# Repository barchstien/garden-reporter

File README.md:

[TOC]

# Overview

Collect data about the garden (soil humidity, luminosity and temperature), that is gathered via xbee link to the collector, for storage and visualisation.

Control and measure water flow. It flows when it is programmed to, or when manually triggered for a set duration.

Xbee modules are configured to :
 - cycle sleep to probe every 15min and stay ON for around 100 msec
 - send data to the collector

## UI and Configuration
 * Collector is configured via YAML, see [collector](/collector/) folder
 * Probes are configured when deployed, by uploading the profile (see profile*.xpro files)
 * Visulisation via Grafana
 * Water-control polls the set program every time it reports water flow
 * Water flow program is configured via web UI

# Probe
More doc about probe in [probe/](/probe)

# Collector
More doc about collector in [collector/](/collector)

# Water-control
More doc about water-control in [water-control/](/water-control)

# grafana-dashboards
Collection of grafan dashboards, exported as JSON, [here](/grafana-dashboards)

# resources
Images and diagrams

# IRL
The system has been running as a prototype since autumn 2022. Thought, after 2 months, the deployed probes started to randomly block, ie not wake up anymore, until it was rebooted. It got fixed only after changing the sleep switch (mosfet) from low side to high side. Cutting the low side was leading some voltage values to go beyond Xbee specs.

The v2 probe have been running since early february 2023. Two other probes have been deployed in mid-february and mid-april 2023. As of end of july 2023, they all perform within nominal parameters.

So far, I have used a COTS water programmer (jardibric PNR16). Which has been working fine. Thought it cannot be programmed to water at a chosen time, nor can it be easily triggered randomly without messing with the set program.

Water flow is also measured using a mechanical water counter found in the local hardware store.

## Visualisation

## Probe

## Collector

## Water-control
Coming soon

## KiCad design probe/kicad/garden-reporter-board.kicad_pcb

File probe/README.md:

# Overview

## Features
 - Probe for :
   - soil humidity
   - air temperature
   - luminosity
   - battery level
 - 6 month+ battery (1 year). See **probe-board-power-use.ods**
 - Report to collector
   - via xbee 2.4GHz 802.15.4
   - every 15min using cycle sleep

Kicad files are in **probe/kicad** folder  
Components datasheet are in **probe/datasheet** folder  

## Board 3d view

# Mechanic and water consideration
 - case should be wateproof
   - plastic bottles are inexpensive and water proof
     - bottom is filled with gravel for stability and in case of leak
   - sensors are attached to case
   - wires from sensors to probe board are water resistent
     - use plumbing goo/joint/paste
   - sensors are environment protected :
     - luminosity is already in epoxy case, wire nail polished
     - temp and wires are nail polished
     - soil moisture bottom is (home made) epoxy coated (water + abrasive)
     - soild moisture top is nail polished

# Components
**Note :** [XXX-XX] : mouser order number

## Xbee
 * XB24CAPIT-001, TH, s2c 802.15.4 [888-XB24CAPIT-001]
    - give 1uF and 8pf cap on supply
    - good keepout (bigger better, no gnd plane up), for pcb antenna
 * usb adapter
    - usb explorer board from sparkfun WRL-11812 [474-WRL-11812] 26.33E
    - dfrobot DFR0050 [426-DFR0050] 18.95E

## Switch
 * TN0702N3-G, can switch 20V, on at 1V, 0.1uA stdby  
   1.53E [689-TN0702N3-G]  
 * Use flywheel diode to protect mosfet from switched inductive load  
   SB130 [637-SB130]
 
## Battery 
 * 4x AA Nimh 2000mAh low self-discharged
   - Accus hybrides Aeonium - 2100mAh 8E for 4, 85% after 1 year
   - Energizer accu recharge extreme 2000mAh 8.6E for 4
 * 4x battery holder 58x31x28 12BH343D-GR [12BH343D-GR]
   OR 534-2476 with snap-on ?  
 Nimh nominal/min/max voltage 1.2/0.9/1.5  
 with 4 cells 4.8/3.6/6V 

## 3.3V voltage regulator
 * MCP1700-3302E/TO 0.5E [579-MCP1700-3302E/TO]  
   Vin 2.3 to 6V, Vdrop typical 178mV, max 350mV  
   250 mA max output  
   Use 1uF co at output (and 1 at input ?)  
 
## Soil moisture sensor
Capacitor sensor  
  * SEN0193 DFRobot 7.9E [426-SEN0193]  
   |--> Protect with nail polish
   |--> been using that one at first. Wire wares off with UV  
        nail polish coating seams to hold fine after 1.5 year  
  * SEN0308 DFRobot 15E [https://wiki.dfrobot.com/Waterproof_Capacitive_Soil_Moisture_Sensor_SKU_SEN0308]  
   |--> Now uses that one, goes deeper, better wire, only nail polish coat the PCB edge
   |--> Use extra 55KOhm in serie of signal, solder in wire  
        This gives ADC values around [75; 800]  
  * 3.3V 5mA  
  * **Warning** some cheapper alternative exists but aren't documented, nor reliable  

## Temp sensor
 * TMP36GT9Z [584-TMP36GT9Z] 1.81E  
   Must add O.1uF cap, very close to device, ie on wire

## Photo transistor
 * TEPT5700 [782-TEPT5700]  
   Use with 5K resistor for outside use with diffuser, measure U, then I = U/R  
   From I, get Lux, using calibration with a ref lux meter  
 The value of R will set the sensibility and saturation level  
 Use with a diffuser, to mitigate the effect of the angle towards the light source  
 
 For inside use, use a higher R value. 
 Aiming 5000 Lux max inside, which is 1/10 of outside max use
 Outside uses 5K --> use 50K --> only have 2x 20K

## Battery level sensor
 * Add battery level check with voltage divider  
   with 2x 10K resitor 1%  
   with zener diode 1N4620 3.3V, [610-1N4620BK]

## Connector
 * sensor to board, 3ways
  - 70543-0002 [538-70543-0002] pcb straigth header  
    70543-0107 for even more gold plating !
  - 79758-0011 [538-79758-0011] crimped wire, 30cm, 22awg
  - 50-57-9403 [538-50-57-9403  ] cable mount
 * battery to board, same with 2 pins
   [538-70543-0106]
 * Use kicad Molex_SL_171971
 
## Case
 * bicycle bottle, ~750mL, 20cm high, 7cm diameter

## Various
 * R 10K 1% metal film : [603-MFR-25FRF5210K]
 * c 10uF ceramic : [710-860010472002] 25VDC 85degC max
 * C 1uF ceramic : [810-FG18X7R1E105KRT0] 25VDC
 * c 8.2 pF ceramic : [80-C315C829D2G] 200VDC

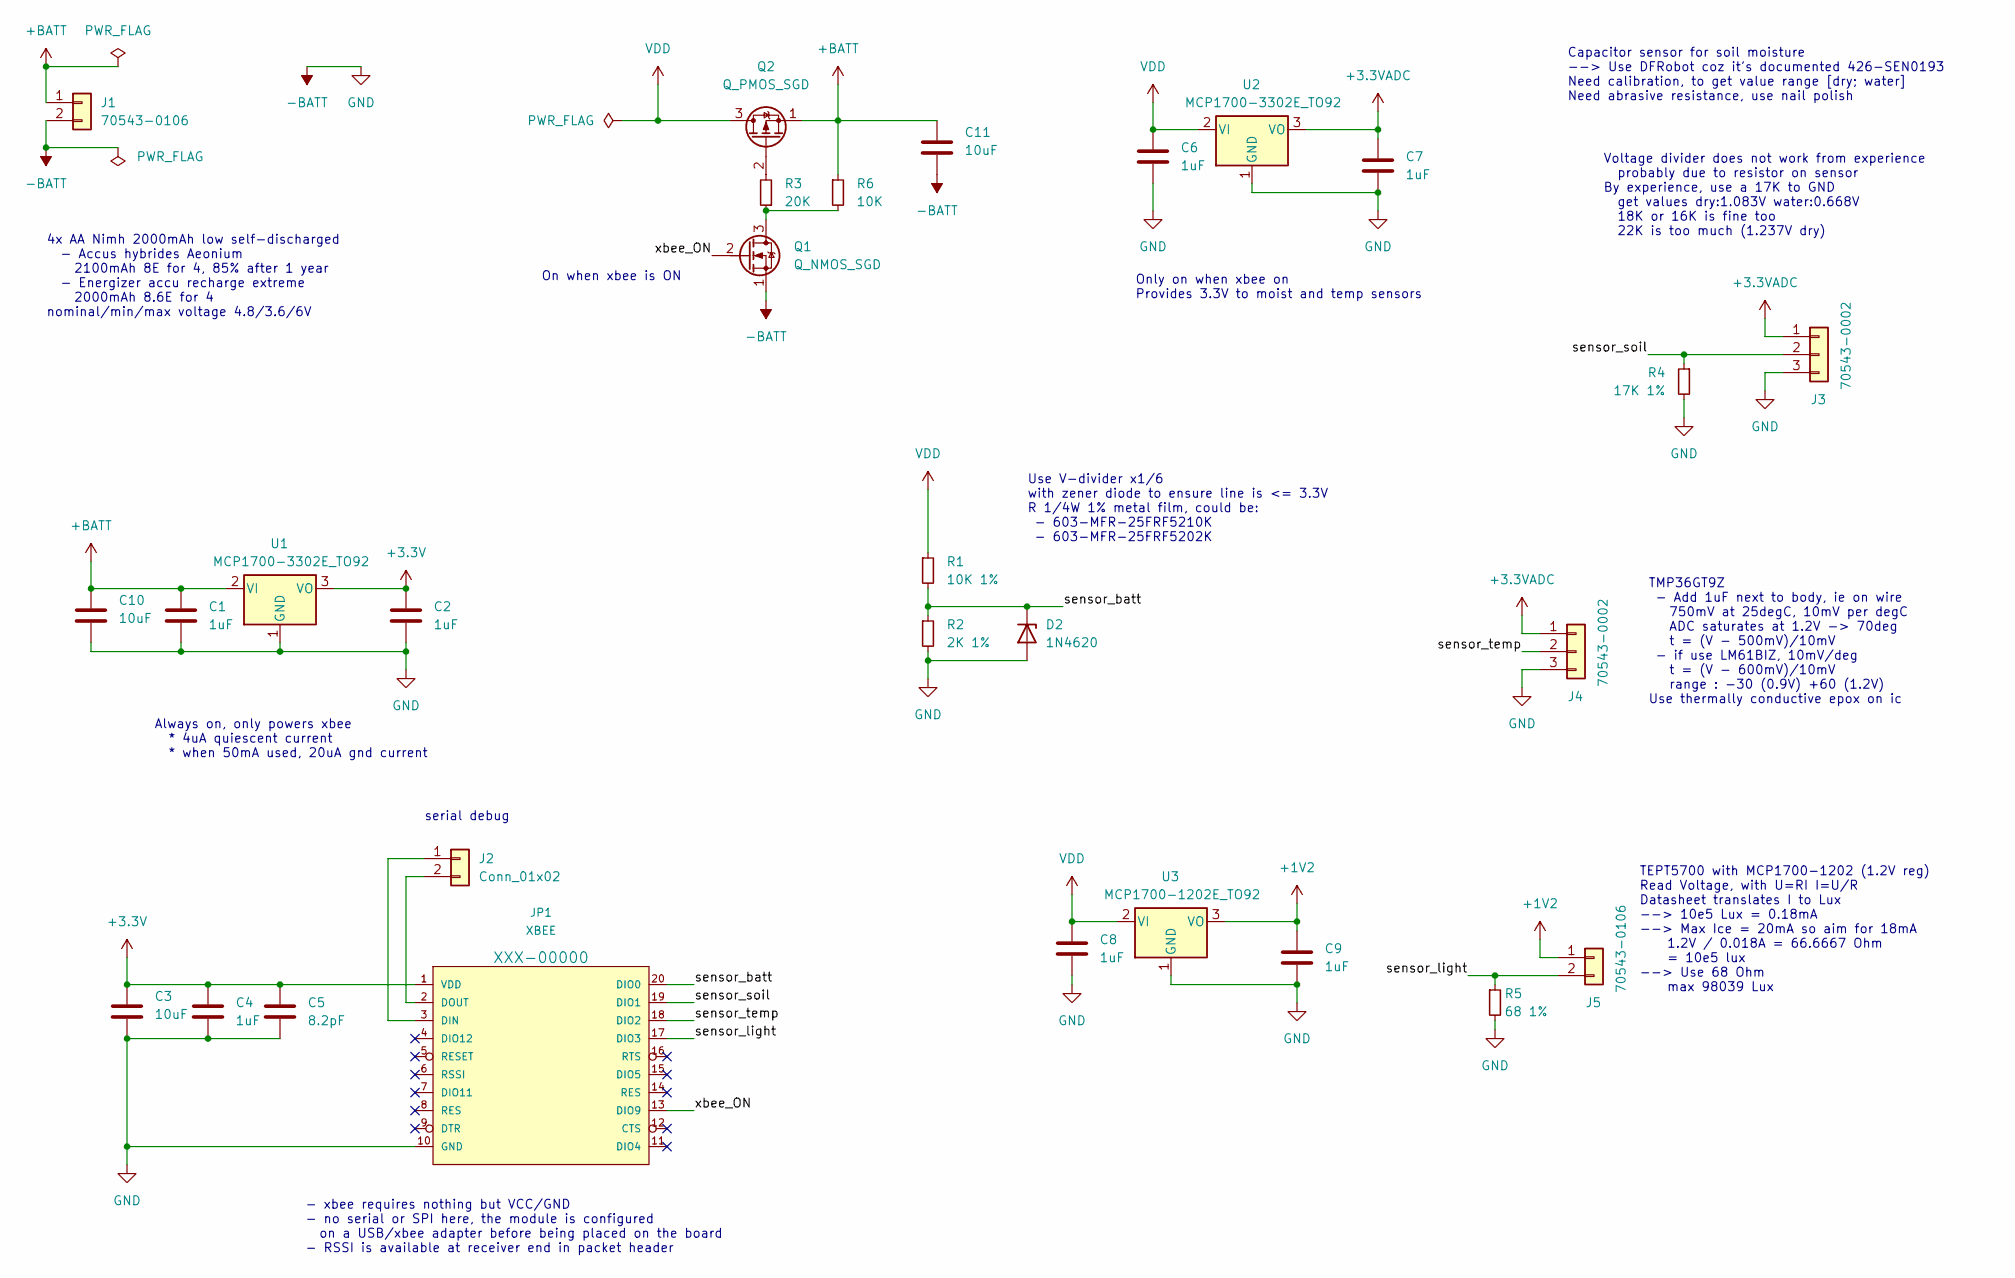
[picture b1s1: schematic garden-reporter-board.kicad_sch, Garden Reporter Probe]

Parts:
C1, C2, C4, C6, C7, C8, C9: 1uF; C_Disc_D3.0mm_W2.0mm_P2.50mm; mouser FG18X5R1H105KRT06
C3, C10, C11: 10uF; C_Disc_D5.0mm_W2.5mm_P2.50mm; mouser 810-FG18X5R1E106MR06
C5: 8.2pF; C_Disc_D3.8mm_W2.6mm_P2.50mm; mouser 80-C315C829D2G
D2: 1N4620; D_DO-35_SOD27_P7.62mm_Horizontal; mouser 610-1N4620BK
J1, J5: 70543-0106; Molex_SL_171971-0002_1x02_P2.54mm_Vertical; mouser 538-70543-0106
J2: Conn_01x02; PinHeader_1x02_P2.54mm_Vertical
J3, J4: 70543-0002; Molex_SL_171971-0003_1x03_P2.54mm_Vertical; mouser 538-70543-0002
JP1: XBEE; mouser 710-62001011821
Q1: Q_NMOS_SGD; TO-92_Inline; mouser 689-TN0702N3-G
Q2: Q_PMOS_SGD; TO-92_Inline; mouser 689-VP3203N3-G
R1: 10K 1%; R_Axial_DIN0207_L6.3mm_D2.5mm_P7.62mm_Horizontal; mouser 603-MFR-25FRF5210K
R2: 2K 1%; R_Axial_DIN0207_L6.3mm_D2.5mm_P7.62mm_Horizontal; mouser 603-MFR-25FRF522K
R3: 20K; R_Axial_DIN0207_L6.3mm_D2.5mm_P7.62mm_Horizontal; mouser 603-MFR-25FRF5220K
R4: 17K 1%; R_Axial_DIN0207_L6.3mm_D2.5mm_P7.62mm_Horizontal; mouser 603-MFR-25FTF52-17K
R5: 68 1%; R_Axial_DIN0207_L6.3mm_D2.5mm_P7.62mm_Horizontal; mouser 279-LR0204F68R
R6: 10K; R_Axial_DIN0207_L6.3mm_D2.5mm_P7.62mm_Horizontal; mouser 603-MFR-25FRF5210K
U1, U2: MCP1700-3302E_TO92; TO-92_Inline; mouser 579-MCP1700-3302E/TO
U3: MCP1700-1202E_TO92; TO-92_Inline; mouser 579-MCP1700-1202E/TO

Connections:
+1V2: C9.1, J5.1, U3.3 (VO)
+3.3V: C2.1, C3.1, C4.1, C5.1, JP1.1 (VDD), U1.3 (VO)
+3.3VADC: C7.1, J3.1, J4.1, U2.3 (VO)
+BATT: C1.1, C10.1, C11.1, J1.1, Q2.1 (S), R6.1, U1.2 (VI)
-BATT: C1.2, C2.2, C3.2, C4.2, C5.2, C6.2, C7.2, C8.2, C9.2, C10.2, C11.2, D2.2 (A), J1.2, J3.3, J4.3, JP1.10 (GND), Q1.1 (S), R2.2, R4.2, R5.2, U1.1 (GND), U2.1 (GND), U3.1 (GND)
/sensor_batt: D2.1 (K), JP1.20 (DIO0), R1.2, R2.1
/sensor_light: J5.2, JP1.17 (DIO3), R5.1
/sensor_soil: J3.2, JP1.19 (DIO1), R4.1
/sensor_temp: J4.2, JP1.18 (DIO2)
/xbee_ON: JP1.13 (DIO9), Q1.2 (G)
unnamed: J2.1, JP1.3 (DIN)
unnamed: J2.2, JP1.2 (DOUT)
unnamed: Q1.3 (D), R3.1, R6.2
unnamed: Q2.2 (G), R3.2
VDD: C6.1, C8.1, Q2.3 (D), R1.1, U2.2 (VI), U3.2 (VI)

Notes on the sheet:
- xbee requires nothing but VCC/GND - no serial or SPI here, the module is configured on a USB/xbee adapter before being placed on the board - RSSI is available at receiver end in packet header
Voltage divider does not work from experience probably due to resistor on sensor By experience, use a 17K to GND get values dry:1.083V water:0.668V 18K or 16K is fine too 22K is too much (1.237V dry)
Use V-divider x1/6 with zener diode to ensure line is <= 3.3V R 1/4W 1% metal film, could be: - 603-MFR-25FRF5210K - 603-MFR-25FRF5202K
Always on, only powers xbee * 4uA quiescent current * when 50mA used, 20uA gnd current
4x AA Nimh 2000mAh low self-discharged - Accus hybrides Aeonium 2100mAh 8E for 4, 85% after 1 year - Energizer accu recharge extreme 2000mAh 8.6E for 4 nominal/min/max voltage 4.8/3.6/6V
Only on when xbee on Provides 3.3V to moist and temp sensors
TMP36GT9Z - Add 1uF next to body, ie on wire 750mV at 25degC, 10mV per degC ADC saturates at 1.2V -> 70deg t = (V - 500mV)/10mV - if use LM61BIZ, 10mV/deg t = (V - 600mV)/10mV range : -30 (0.9V) +60 (1.2V) Use thermally conductive epox on ic
On when xbee is ON
Capacitor sensor for soil moisture --> Use DFRobot coz it's documented 426-SEN0193 Need calibration, to get value range [dry; water] Need abrasive resistance, use nail polish
serial debug
TEPT5700 with MCP1700-1202 (1.2V reg) Read Voltage, with U=RI I=U/R Datasheet translates I to Lux --> 10e5 Lux = 0.18mA --> Max Ice = 20mA so aim for 18mA 1.2V / 0.018A = 66.6667 Ohm = 10e5 lux --> Use 68 Ohm max 98039 Lux

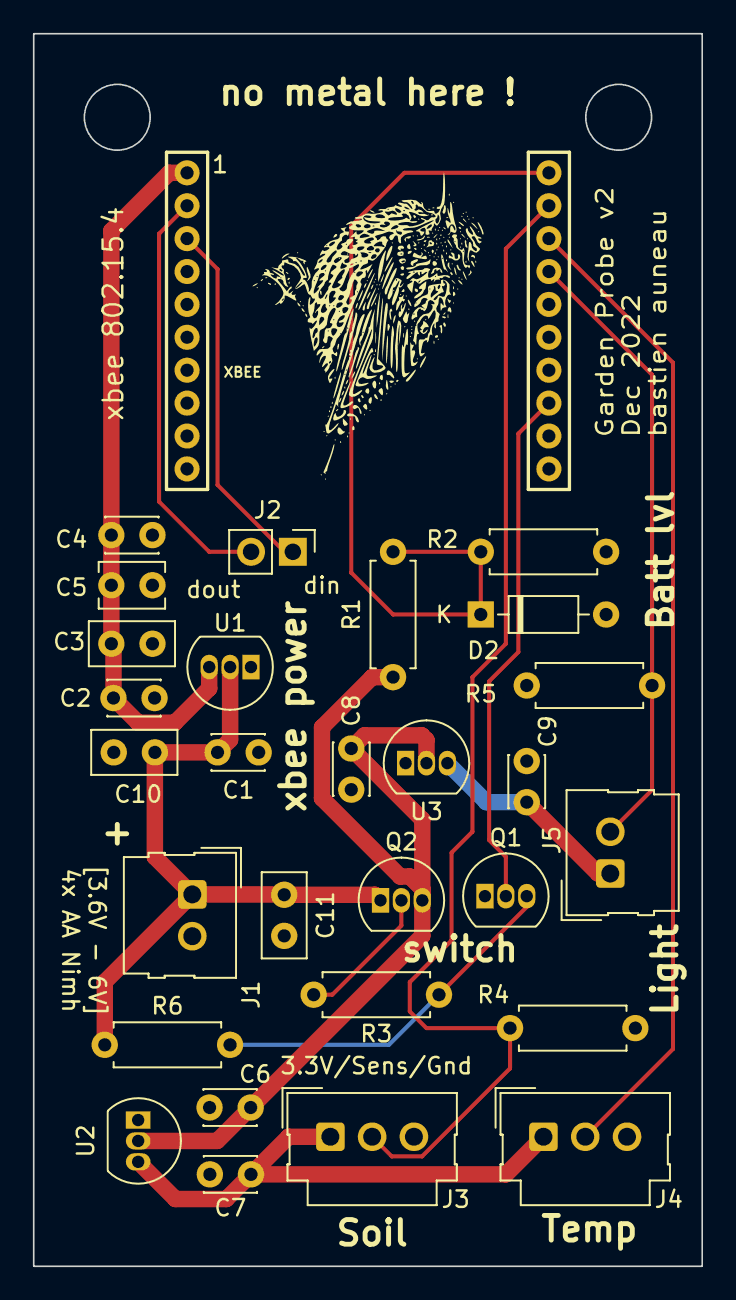
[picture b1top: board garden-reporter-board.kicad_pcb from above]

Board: 2 copper layers, 40.6 x 74.9 mm, 29 parts (0 on the bottom side), 15 nets.

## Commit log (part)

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2022-08-12 Initial commit, removed previous history which was bloated with kicad backup and cache files
2022-08-21 Feature/probe pcb edge and routing
2022-08-21 Smaller mouting holes
2022-08-22 Fix bad flyback diode connection, move xbee edge drawing to fron silkscreen
2022-08-22 Add artichoke picture, add and ùake pretty silkscreen comments
2022-08-22 Pretty
2022-08-29 Feature/better doc
2022-09-04 Doc on not using telegraf
2022-09-06 Start collector, re-organize folders
2022-09-24 Feature/v divider for sensors
2022-09-24 Fix Xbee frame decoder bug, started SerialHub, add doc on xbee range
2022-09-24 Install pyyaml, load probes calib from yaml, and serial config and influxdb config from yaml too
2022-09-25 Better doc
2022-10-01 Add serial_hub
2022-10-02 serial_hub provides r a,d w queues. tcp_listener basic fwd
2022-10-03 Collector works, but XCTU can't connect
2022-10-03 tcp serial working
2022-10-03 Use custom channel id and PAN id, use 64bit addressing
2022-10-03 Use 64 bit ADC frame (x82)
2022-10-04 Notes on xbee API use
2022-10-12 Basic blocks decoding frames to dict, empty shell with interface for...
2022-10-12 sleep more, use less CPU (2.2 to 0.8%)
2022-10-12 Add XbeePopulationModel methods to hold or release endpoint in config. Start serial_tcp_client to handle creation and config on client side
2022-10-12 TcpListerner has ref to xbee popo model, fix socat call on tcp client script
2022-10-12 Better message
2022-10-12 SerialHub 1 thread to read and one to write, using blocking call for minimal CPU use
2022-10-12 socket accept blocking call and cancel with shutdown()
2022-10-12 serial hub read all available at once
2022-10-13 Use 1 thread to read 1 to write in TCP Listener, remove some traces
2022-10-13 Working TCP Listener that holds in config and exits properly
2022-10-13 serial-tcp-client has now help(), extracts all args from CLI, and runs socat
2022-10-13 TCP Listener waits for 8 bytes, and can cancel and fall back to normal mode
2022-10-13 seria tcp client sends MAC, listener receives it
2022-10-14 Tcp to serial have client and server negotiating for MAC to hold, and to wait for endpoint to be up and help (no cycle sleep)
2022-10-14 Send enable/disable Cycle Sleep when config mode is requested
2022-10-14 BEtter display reply status
2022-10-14 Encode value when needed, for SM AT cmd only
2022-10-14 Apply changes option when set/unset cycle sleep mode, do not wait for target when request mac 0
2022-10-15 Cleanup collector doc
2022-10-15 pipenv lock
2022-10-16 TODOs and docs on V-divider for light sensor
2022-10-19 Add basic Dockerfile add calib value for soil moisture on proto
2022-10-19 Pretty tcp serial client waiting msg
2022-10-29 Map soil moisture to percentage
2022-10-31 Docker working, update doc, fix showing all past errors on startup
2022-10-31 Notes on influxdb backup
2022-10-31 Add to light sensor V reg to 1.2V, adjust light R properly, fix layout accordingly
2022-10-31 Clean up old TODO, warning on soil moisture and V-divider
2022-10-31 Comment on soil moisture sensor and V-divider
2022-11-10 Fix trace bug
2022-11-10 Doc on batery life expectation
2022-11-11 Add profile cycle sleep 15min with 100msec sleep tiemout
2022-11-11 Run python with -u as unbuffered to get anything with docker logs
2022-11-11 Estimation max days by projection from measured use
2022-11-11 Working state ! Just pulling ADC once, been hacking model, and tuning sleep values
2022-11-11 Comments on hacks
2022-11-13 Xbee population model is executed by collector thread, hack message flow to only sample ADCs
2022-11-14 Poll errors when timeout occrs (24h), write error to db when there is, cleanup
2022-11-14 Update last error timestamp when recv error msg
2022-11-15 Collector uses blocking get() from Q, awakening is now down to 30-35msec per request
2022-11-15 Fix voltage output range of soil moist sensor, 1.2V to light sensor
2022-11-15 Fix crash and clean README
2022-11-17 Fix xbee not being released from config (ie not back to cycle sleep), due to population model being called only when frame is received. Now executing population model on frame RX timeout
2022-11-18 Try ax+b calibration
2022-11-18 Use ax+b to calibrate temp
2022-11-19 Adjust dry value
2022-11-22 Add exported dashboard json
2022-11-27 Light is percet
2022-11-28 More profile and dashbord backup
2022-11-28 Add lm61 and xbee grove usb datasheet
2022-12-09 Better doc on influxdb backup/restore
2022-12-09 Fix bug on TCP server when bad connection happen
2022-12-10 Add profile with cycle sleep disabled
2022-12-10 Add second xbee unit to config
2022-12-12 Better msg, dummy mac for 1s device
2022-12-14 Smaller profile. Re-number sensor mosfet pins properly
2022-12-18 Re-enable 1st unit MAC
2022-12-18 Cleanup notes in README
2022-12-18 Print frame received out of awakening, remove extra frame sent after awakening
2022-12-18 Add ceriamic cap for xbee and heavy load sensors, better routing of voltage regulator capacitors, more compact outline
2022-12-18 Add ceramic cap datasheet
2022-12-18 Also pull xbee for supply level, every time CC error is pulled, ie every 24h
2022-12-18 Routing decouple cap
2022-12-18 Fix bug and Better message on influx-db error
2022-12-23 Use high side switch, chose new components and footprints, layed out but no route, use GND plane, add doc and datasheet
2022-12-23 Route all
2022-12-24 Finish and verifiy routing, finish and verify BOM
2022-12-24 Add garden probe v2 gerber files
2023-02-07 High side switch working fine, fix few comments
2023-02-07 Latest profile, probably some tweaking
2023-02-07 Rename timeout for polling erro cnt
2023-02-07 Notes taken while investigating before going for high side switch
2023-02-07 Translate light ADC read into Lux
2023-02-08 Use v2 config for battery v divider, soil read range, default temperature formula
2023-02-08 Remove light coefficient from yaml and data_calibrator
2023-02-14 Add grafana dashboards
2023-02-14 Add R config to light sensor
2023-02-15 Add location as tag, force data type in influxdb write
2023-02-15 Update Grafana dashboards with location tag support
2023-02-16 Use windowPeriod and better names for grafana dashboards json export files
2023-02-26 Clean up xbee profiles
2023-02-26 Remove influxdb dashboards, replaced by grafana
2023-02-26 Remove old grafana dashboards
2023-02-26 Better grafana dashboards that inludes location, links, etc
2023-02-26 Cleanup
2023-02-26 More cleanup
2023-02-26 pip install as user, fix user home dir bug, cleanup
2023-02-26 Calibrate noisetier
2023-03-31 Calibraet light with ref
2023-04-03 Lower immerged value probe 1
2023-05-18 Unit #3 and more calibration
2023-05-21 Remove non used python yaml lib from pipenv
2023-05-21 New moist calibration for noisetier and potager nord
2023-07-29 Better organise doc in sub-folders
2023-07-29 Better alignment of probe doc
2023-07-29 TODO
2023-07-30 Basic html page, from a discussion with chatgpt
2023-07-30 Just before asking chatgpt to : make it look cool
2023-07-30 A bit larger box
2023-07-30 ASCII art git diff
2023-07-30 Move html to python folder
2023-07-30 Basic python server serves modified html file
2023-07-30 Add more paths to poll and update
2023-08-02 Basic web server, handles requests, feed prams
2023-08-02 Pretty ascii
2023-08-07 /report gets values and ecoes back as json
2023-08-07 Add arduino workspace
2023-08-08 Basic structure and main function for wifi and pin settings
2023-08-09 basic http GET and basic valve control
2023-08-15 Doc on power use. Basic buttons working. Add TimeLib simplified biiig time, better interface
2023-08-15 time_lib better naming and simplified
2023-08-16 Proto to get time from http server
2023-09-03 Test mode and doc on pin numbering vs arduibox
2023-10-10 Button test success
2023-10-14 Add robot favicon
2023-10-22 Basic debug loop
2023-11-25 Add unit #4, consider unit without soil recording
2023-11-25 Fix end point profile, doc
2023-11-29 Better light calibration for indoor unit
2024-02-24 Maison unit better calib
2024-06-04 Http server for human and machine first proto
2024-06-07 Basic request and replay working between water-controller and server
2024-06-07 wifi client reports to server and propagate command
2024-06-08 Battery, buttons, time sync, report all work
2024-06-11 Schedule can be config from WEB UI, and propagates to arduino. Arduino reports voltage and water volume
2024-06-13 Better local clock vs epoch time from server
2024-06-14 Better epoch sync, clean up, start bringing real status of arduino to web UI
2024-06-14 time sync working like a charm, use msec counter to avoid stacking up rounding errors
2024-06-15 Display valve status
2024-06-15 Report valve status, count wraps to provide uptime
2024-06-15 Usable proto, stop using cgi even for POST
2024-06-16 Longer valve pulse (1sec), longer max duration (1.5h), check allow water button when schedule watering, led off fix
2024-06-18 Calibrate water counter, remove debug traces, use Threading HTTP server, count sum of drifts
2024-06-21 Many bug fixes (re-schedule, led, time sync, http response wait
2024-06-23 Retry HTTP request few times before giving up
2024-06-23 Less log
2024-06-23 Way clearer local vs epoch clock, use RTC backeend for epoch, update value from server when over threshold, local_clock_t reconstructs higher bits to hide wrap
2024-06-23 Remove python basee HTTP server log
2024-06-24 15min between HTTP reports, better scale web human UI to mobile phone
2024-06-24 Better calib, set max size for container log in restart script
2024-06-24 First proto, should disable other modeules for tests
2024-06-24 Write water web control volume and battery in db
2024-06-26 Report when water triggered manually, use RTC clock coz millis() drift wayyyy to much
2024-06-26 Use named volume for water-web-control config, fix docker files rights, write water usage in db
2024-06-26 Remove some print in water web server
2024-06-26 Fix last report bug when config not applied
2024-07-02 Avergae read battery, adjust safe limit
2024-07-02 Led uses less steps to fade
2024-07-02 Check battery while watering, fix bug where HTTP report happens all the time when server is down
2024-07-02 Set RAM max use and named volume to podify and keep files across container start/stop
2024-07-05 weblog uses int64 unix timestamps, coded as hex, prettyfy weblog for human, report also water schedule on/off
2024-07-05 Add temp from RTC and RSSI from wifi to influxdb
2024-07-05 Revert server IP to .66 and sleep duration to 15min
2024-07-05 Add gerber used to generate v2 PCB, kicad update to v 7.0
2024-07-08 More WEB_LOG for manual trigger and/or watering being skipped, prettify too
2024-07-11 Notes on soil moisture sensor (new sensor, extra R)
2024-07-12 Add calibration mode, all config yaml are now in a named volume, delay sampling until new soil moisture sensor has settled
2024-07-28 More comments on pulse length, disabled water on/off retries and init with multiple off. Wires are soldered, current pulse is working fine for 5 tries. Checkpoint before getting pulse secured once an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
2024-08-11 Back to working on/off valve stage
2024-08-13 docker compose with influxdb, grafana and collector
2024-08-13 Doc and cleanup
2024-08-14 Restrict resources more
2024-08-14 Edit grafana JSON dashboards with updated bucket name
2024-08-14 Remove un-used secrets from docker compose file
2024-08-14 Valve working fine
2024-08-14 Add scripts to compile/upload/serial to arduino from local
2024-08-14 Add datasheets for valve and RTC
2024-08-14 Add Water dashboard json model
2024-08-16 Doc and grafana dashboard backups
2025-03-07 Remove battery
2025-03-08 Update doc about new 15V power supply and ball valve
2025-03-08 valve_t is now ball_valve_t, ni more pulses and retry and flow feedback
2025-03-09 Update main water dashboard with close up on last 12h
2025-03-09 Valve polarity set, do update ball valve status
2025-03-09 Comment out frame id logic with xbee (continuity counter)
2025-03-09 Docs, small fixes for deploy/docker compose, update main dashboard
2025-03-09 Update grafana dashboard
2025-05-08 Calibrate Unit #1
2025-05-08 Light calibration intercept at 0
2025-05-12 Disable soil moisture from config
2025-05-13 Display future date in date picker
2025-05-14 Remove battery from water-web-control
2025-05-16 Remove battery from html only
2025-08-26 Backup grafana views
2025-08-26 Manual fine tune of calib
2025-11-02 Good humidity calibration
